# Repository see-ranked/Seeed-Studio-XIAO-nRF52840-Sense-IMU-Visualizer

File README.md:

# XIAO nRF52840 Sense IMU Display Project

Seeed Studio XIAO nRF52840 SenseのLSM6DS3 IMUセンサーからデータを読み取り、リアルタイムで表示するプロジェクトです。

## 🌐 デモページ（GitHub Pages）

**インストール不要でブラウザから直接お試しいただけます：**

👉 **[https://see-ranked.github.io/Seeed-Studio-XIAO-nRF52840-Sense-IMU-Visualizer/visualizer/](https://see-ranked.github.io/Seeed-Studio-XIAO-nRF52840-Sense-IMU-Visualizer/visualizer/)**

| 接続方法 | 対応ブラウザ | 説明 |
|----------|------------|------|
| 📡 Serial (USB) | Chrome / Edge | USB接続したXIAOからシリアルデータを受信 |
| 📶 Bluetooth | Chrome / Edge | BLE経由でワイヤレスにデータを受信 |

> [!NOTE]
> GitHub PagesはHTTPS配信のため、Web Serial APIおよびWeb Bluetooth APIが追加設定なしで動作します。

## 🎯 機能

- ✅ **6軸IMUデータ取得**: 3軸加速度計 + 3軸ジャイロスコープ
- ✅ **温度センサー**: 内蔵温度センサーのデータ取得
- ✅ **シリアル出力**: JSON形式でのデータ出力（115200 bps）
- ✅ **3Dビジュアライゼーション**: リアルタイムで姿勢を3D表示
- ✅ **グラフ表示**: 加速度とジャイロのリアルタイムグラフ
- ✅ **Web Serial API**: ブラウザから直接シリアルポートに接続

## 📋 必要なもの

### ハードウェア
- [Seeed Studio XIAO nRF52840 Sense](https://www.seeedstudio.com/Seeed-XIAO-BLE-Sense-nRF52840-p-5253.html)
- USB-Cケーブル

### ソフトウェア
- [Arduino IDE](https://www.arduino.cc/en/software) (v1.8.19以降 または v2.x)
- Chrome または Edge ブラウザ（Web Serial API対応）

## 🚀 セットアップ

### 1. Arduino IDE の準備

#### ボードサポートの追加

1. Arduino IDE を開く
2. **ファイル** → **環境設定** を開く
3. **追加のボードマネージャのURL** に以下を追加:
   ```
   https://files.seeedstudio.com/arduino/package_seeeduino_boards_index.json
   ```
4. **ツール** → **ボード** → **ボードマネージャ** を開く
5. "Seeed nRF52" を検索してインストール

#### ライブラリのインストール

1. **スケッチ** → **ライブラリをインクルード** → **ライブラリを管理** を開く
2. "LSM6DS3" を検索
3. **Seeed_Arduino_LSM6DS3** をインストール

### 2. ファームウェアのアップロード

1. `XIAO_nRF52840_IMU/XIAO_nRF52840_IMU.ino` を開く
2. **ツール** → **ボード** → **Seeed nRF52 Boards** → **Seeed XIAO nRF52840 Sense** を選択
3. **ツール** → **シリアルポート** → 適切なCOMポートを選択
4. **アップロード** ボタンをクリック

### 3. 動作確認（シリアルモニター）

1. **ツール** → **シリアルモニタ** を開く
2. ボーレートを **115200** に設定
3. 以下のようなJSON形式のデータが表示されることを確認:
   ```json
   {"accel":{"x":0.123,"y":-0.045,"z":9.812},"gyro":{"x":0.012,"y":-0.023,"z":0.001},"temp":25.3,"timestamp":12345}
   ```

### 4. Webビジュアライザーの起動

#### 方法1: GitHub Pages（最も簡単・推奨）

インストール不要でブラウザからそのまま使えます：

👉 **[https://see-ranked.github.io/Seeed-Studio-XIAO-nRF52840-Sense-IMU-Visualizer/visualizer/](https://see-ranked.github.io/Seeed-Studio-XIAO-nRF52840-Sense-IMU-Visualizer/visualizer/)**

#### 方法2: Pythonを使用（ローカル）

```bash
cd visualizer
python -m http.server 8000
```

ブラウザで `http://localhost:8000` を開く

#### 方法3: Node.jsを使用（ローカル）

```bash
cd visualizer
npx -y http-server -p 8000
```

ブラウザで `http://localhost:8000` を開く

#### 方法4: 直接ファイルを開く

`visualizer/index.html` をChromeまたはEdgeに直接ドラッグ＆ドロップ

> [!WARNING]
> `file://` から開いた場合、Web Serial APIおよびWeb Bluetooth APIが動作しない場合があります。
> シリアル接続・BLE接続いずれも使用する場合は方法1〜3を使用してください。

### 5. Webビジュアライザーの使用

1. **シリアルポートに接続** ボタンをクリック
2. XIAO nRF52840のポートを選択
3. リアルタイムでデータが表示されます:
   - 3Dモデルがボードの姿勢に合わせて回転
   - 加速度とジャイロのグラフが更新
   - センサー値が数値で表示

## 📊 データフォーマット

シリアル出力は以下のJSON形式です:

```json
{
  "accel": {
    "x": 0.123,  // m/s²
    "y": -0.045,
    "z": 9.812
  },
  "gyro": {
    "x": 0.012,  // °/s
    "y": -0.023,
    "z": 0.001
  },
  "temp": 25.3,  // ℃
  "timestamp": 12345  // ミリ秒
}
```

## 🎨 Webビジュアライザーの機能

### 3Dビジュアライゼーション
- Three.jsを使用した3D表示
- リアルタイムで姿勢（Roll, Pitch, Yaw）を計算
- 相補フィルターによるノイズ除去

### グラフ表示
- Chart.jsを使用したリアルタイムグラフ
- 加速度とジャイロの3軸データを同時表示
- 最大50データポイントを表示

### センサーデータ表示
- 加速度（X, Y, Z軸）
- ジャイロスコープ（X, Y, Z軸）
- 温度
- サンプルレート
- 受信パケット数

## 🔧 トラブルシューティング

### Arduino IDE でボードが見つからない

- USB-Cケーブルがデータ転送対応か確認
- ドライバーが正しくインストールされているか確認
- ボードをリセット（RSTボタンを2回素早く押す）

### IMUセンサーの初期化に失敗

```
ERROR: Failed to initialize LSM6DS3!
```

**原因と対処法:**
- **間違ったボード**: XIAO nRF52840 Sense（Senseあり）を選択しているか確認
- **ライブラリ未インストール**: Seeed_Arduino_LSM6DS3ライブラリをインストール
- **ハードウェア不良**: 別のボードで試す

### Webビジュアライザーで接続できない

**Web Serial API非対応:**
- Chrome または Edge ブラウザを使用
- ブラウザを最新版に更新

**ポートが見つからない:**
- Arduinoのシリアルモニターを閉じる（ポートが占有されている）
- ボードが正しく接続されているか確認

### データが表示されない

- ボーレートが115200になっているか確認
- シリアルモニターでデータが出力されているか確認
- ブラウザのコンソール（F12）でエラーを確認

## 📁 プロジェクト構成

```
Seeed-Studio-XIAO-nRF52840-Sense/
├── XIAO_nRF52840_IMU/
│   └── XIAO_nRF52840_IMU.ino    # Arduinoファームウェア
├── visualizer/
│   ├── index.html                # Webビジュアライザー
│   ├── style.css                 # スタイルシート
│   └── app.js                    # アプリケーションロジック
├── docs/
│   └── SETUP.md                  # 詳細セットアップガイド
└── README.md                     # このファイル
```

## 🎓 技術仕様

### LSM6DS3 IMUセンサー
- **加速度計範囲**: ±2g, ±4g, ±8g, ±16g（デフォルト: ±2g）
- **ジャイロ範囲**: ±125, ±250, ±500, ±1000, ±2000 °/s（デフォルト: ±2000 °/s）
- **サンプリングレート**: 最大1.6 kHz（このプロジェクト: 100 Hz）
- **通信方式**: I2C（アドレス: 0x6A）

### 姿勢推定アルゴリズム
- **相補フィルター**: 加速度計とジャイロのデータを融合
- **フィルター係数**: α = 0.98
- **更新周期**: リアルタイム（約100 Hz）

## 📚 参考資料

- [XIAO nRF52840 Sense Wiki](https://wiki.seeedstudio.com/XIAO_BLE/)
- [LSM6DS3 データシート](https://www.st.com/resource/en/datasheet/lsm6ds3.pdf)
- [Web Serial API ドキュメント](https://developer.mozilla.org/en-US/docs/Web/API/Web_Serial_API)
- [Three.js ドキュメント](https://threejs.org/docs/)
- [Chart.js ドキュメント](https://www.chartjs.org/docs/latest/)

## 📝 ライセンス

このプロジェクトはMITライセンスの下で公開されています。

## 🤝 貢献

バグ報告や機能リクエストは、GitHubのIssuesでお願いします。

## 📧 お問い合わせ

質問や提案がある場合は、Issuesまたはプルリクエストでお知らせください。

---

**Enjoy coding! 🎉**

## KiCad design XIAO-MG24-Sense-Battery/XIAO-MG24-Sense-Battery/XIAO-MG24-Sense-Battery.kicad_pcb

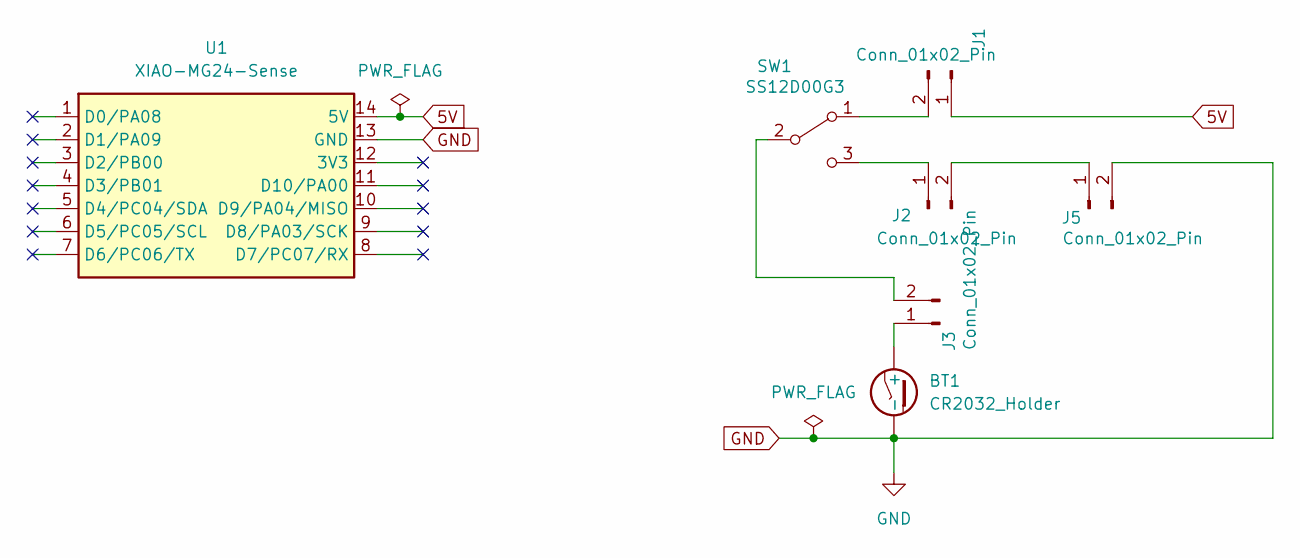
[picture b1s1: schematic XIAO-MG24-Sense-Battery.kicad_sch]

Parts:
BT1: CR2032_Holder; CR2032-Holder
J1, J2, J5: Conn_01x02_Pin; PinHeader_1x02_P2.54mm_Horizontal
J3: Conn_01x02_Pin; PinHeader_1x02_P2.54mm_Vertical
SW1: SS12D00G3
U1: XIAO-MG24-Sense; XIAO-MG24-Sense_10pin

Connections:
5V: J1.1, U1.14 (5V)
GND: BT1.2 (-), J5.2, U1.13 (GND)
unnamed: BT1.1 (+), J3.1
unnamed: J1.2, SW1.1 (NO)
unnamed: J2.1, SW1.3 (NC)
unnamed: J2.2, J5.1
unnamed: J3.2, SW1.2 (COM)

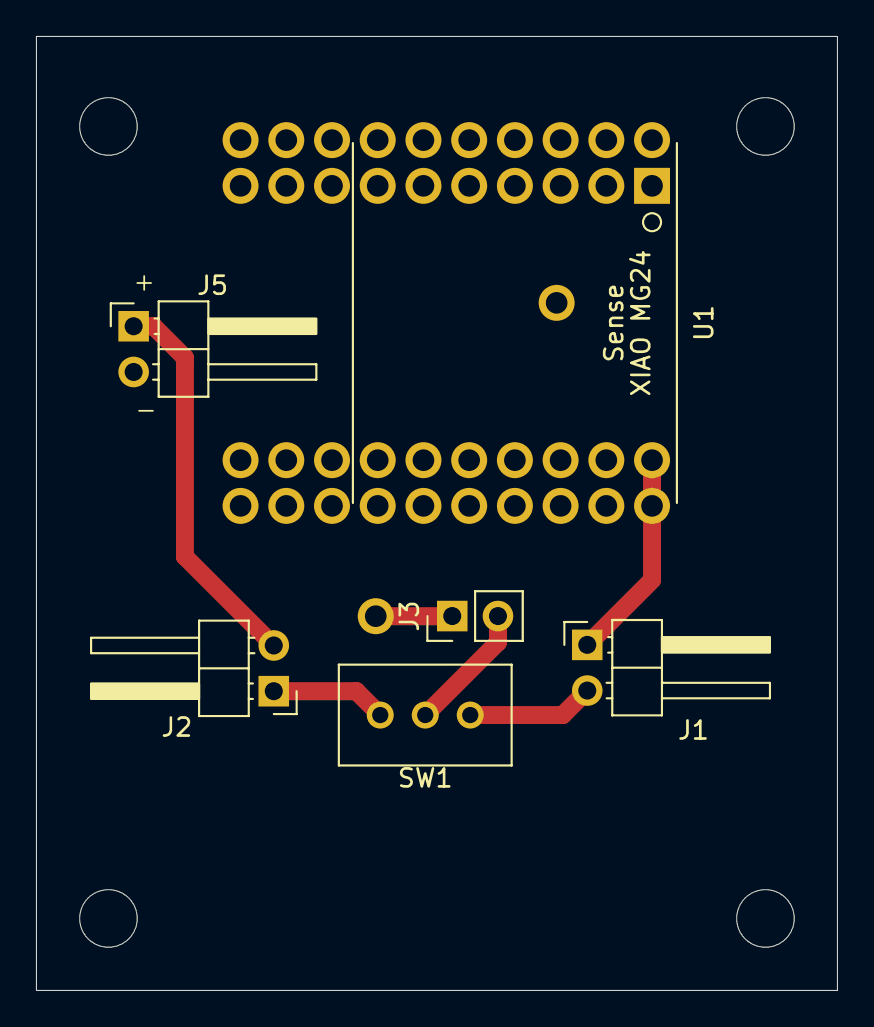
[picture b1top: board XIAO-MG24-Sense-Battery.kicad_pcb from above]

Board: 2 copper layers, 44.5 x 53.0 mm, 7 parts (1 on the bottom side), 7 nets.

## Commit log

2026-01-31 Create new
2026-02-01 Update that adds BLE connection function
    Supports BLE connection with Web Serial API compatible browsers.
2026-02-11 Add code for Seeed Studio XIAO MG24 Sense.
2026-02-14 Added coin cell battery circuit symbols and footprints for KiCad
2026-02-15 Added a circuit to operate "XIAO-MG24-Sense"
    Added a circuit to operate "XIAO-MG24-Sense" with a coin cell battery
2026-02-17 Add case design
2026-02-28 Add gerber data created with Kicad v9.06
2026-03-19 Supports BLE connectivity for XIAO MG24 sense.
2026-03-19 Fix for BLE connectivity on XIAO MG24 sense
2026-03-20 Supports multiple Bluetooth connections.
2026-03-21 Modified PCB Data
